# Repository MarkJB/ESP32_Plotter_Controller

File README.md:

# ESP32 Plotter Controller PCB
 
Released under an MIT licence, no warranty implied or given, use at own risk etc etc.

This is a two axis stepper controller based on the ESP32 and TMC2130 stepper drivers. It is intended to be used with drawing machines and plotters.

See https://github.com/MarkJB/TMC429_Daughterboard_for_ESP32_Plotter_Controller for the TMC429 (Hardware stepper driver contoller) daughter board for this board (plugs into the two stepper motor driver sockets and provides an extra axis and hardware acceleration control.

Firmware https://github.com/MarkJB/Grbl_Esp32 (This is a Fork of Grbl_Esp32, if its out of date, you probably only need the config file from this fork). Tested with standard and corexy kinematics and a solenoid/relay for the spindle.

First board revision A (aka 'Diamiond Chimp'), this board revision B (aka Emerald Dingo)

[Schematic]( https://github.com/MarkJB/ESP32_Plotter_Controller/blob/main/ESP32_Plotter_Controller_Schematic_RevA.pdf )

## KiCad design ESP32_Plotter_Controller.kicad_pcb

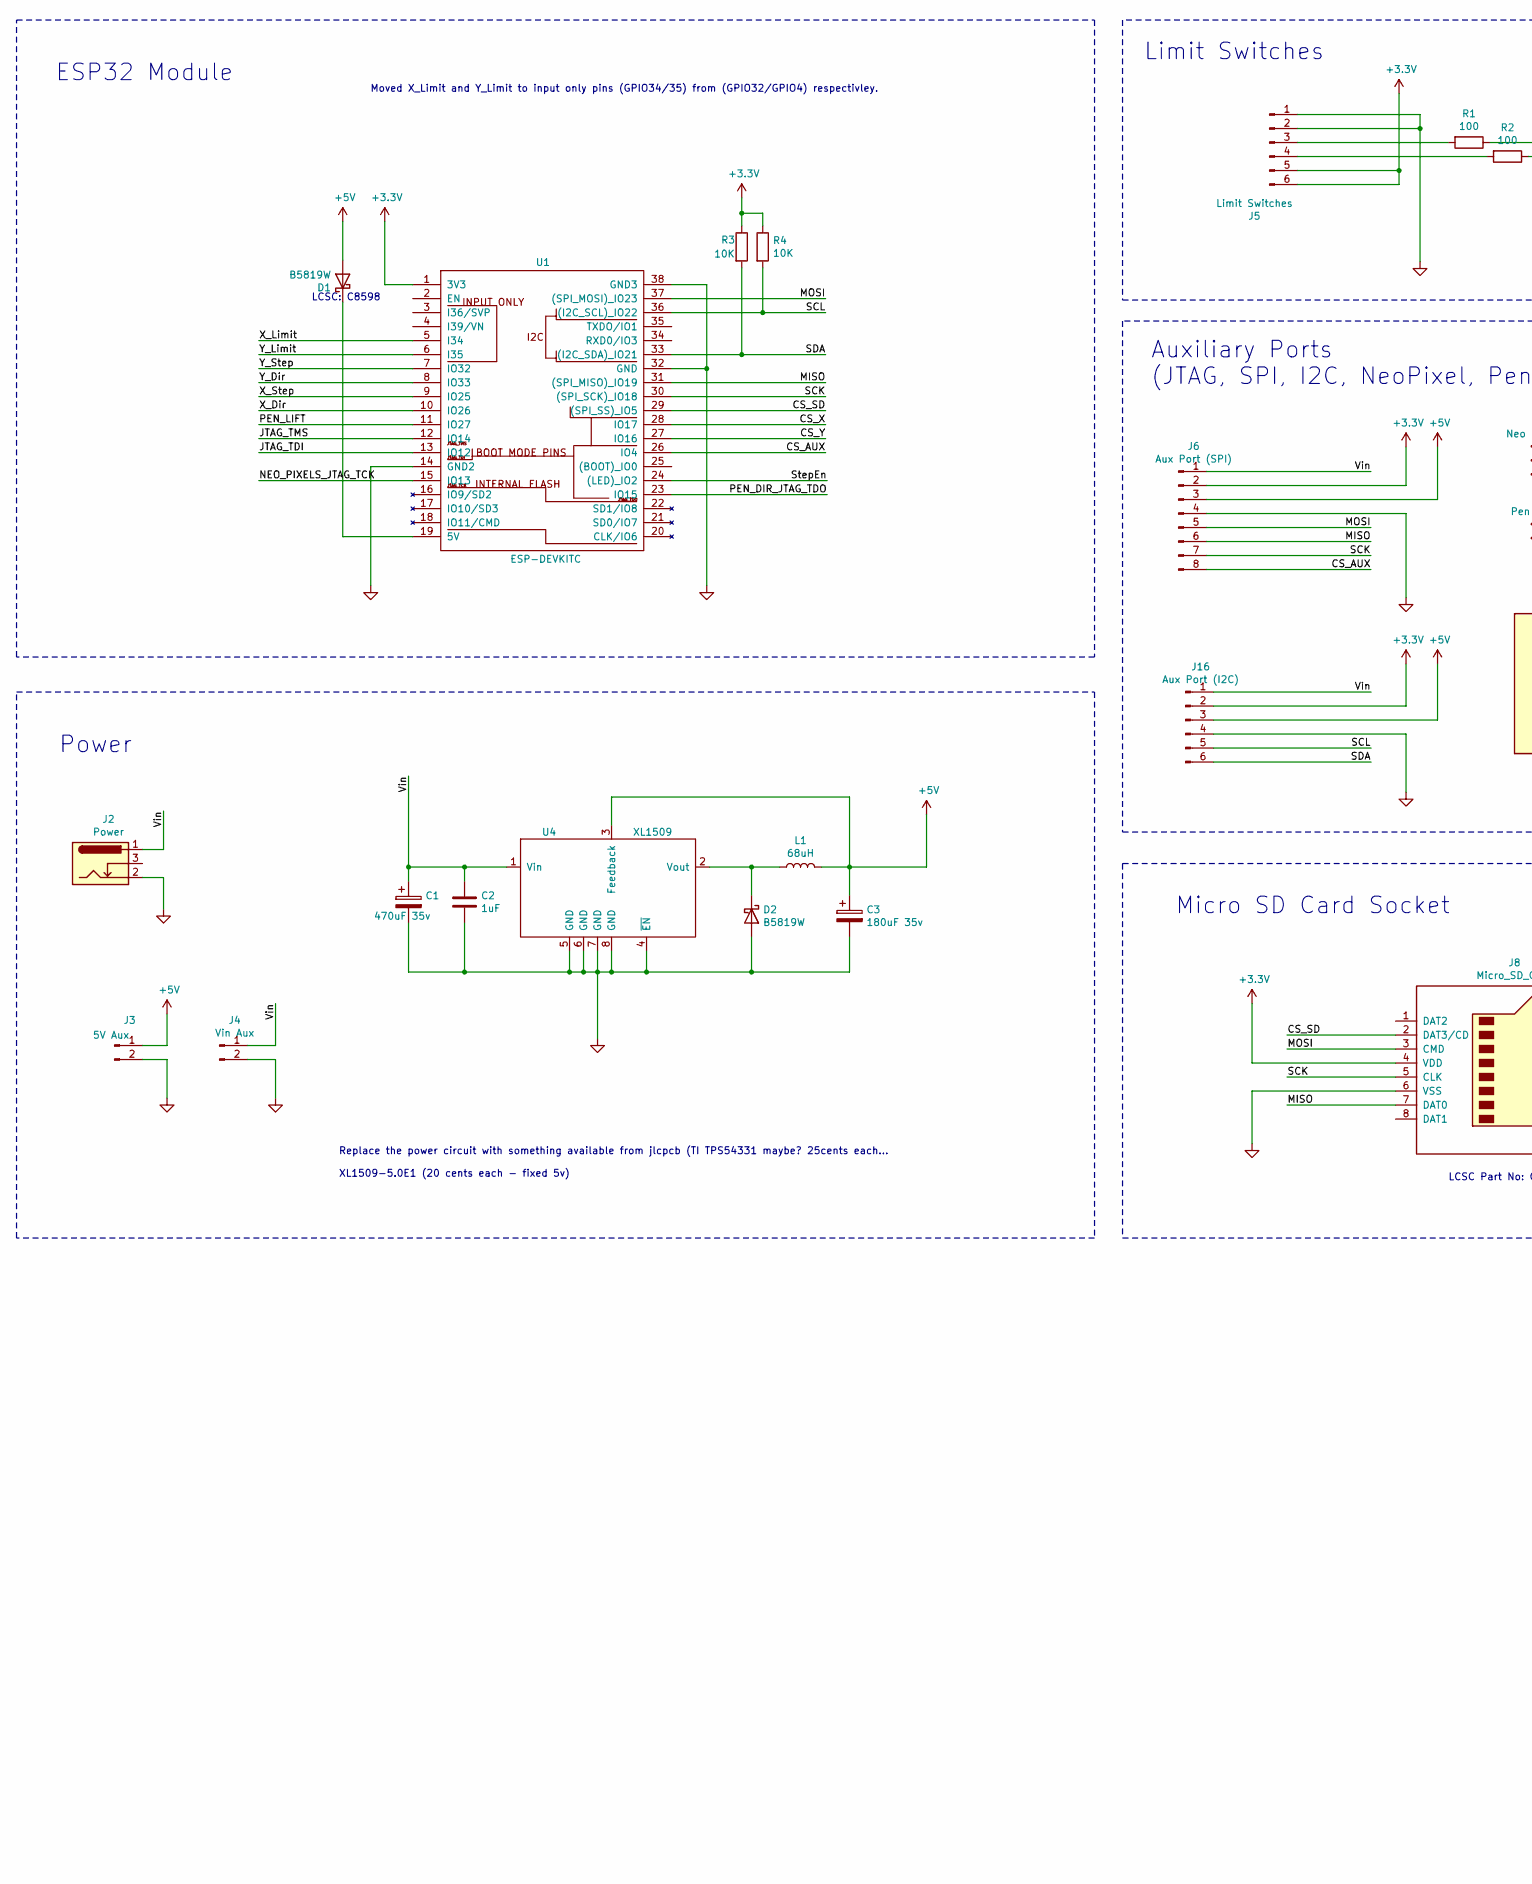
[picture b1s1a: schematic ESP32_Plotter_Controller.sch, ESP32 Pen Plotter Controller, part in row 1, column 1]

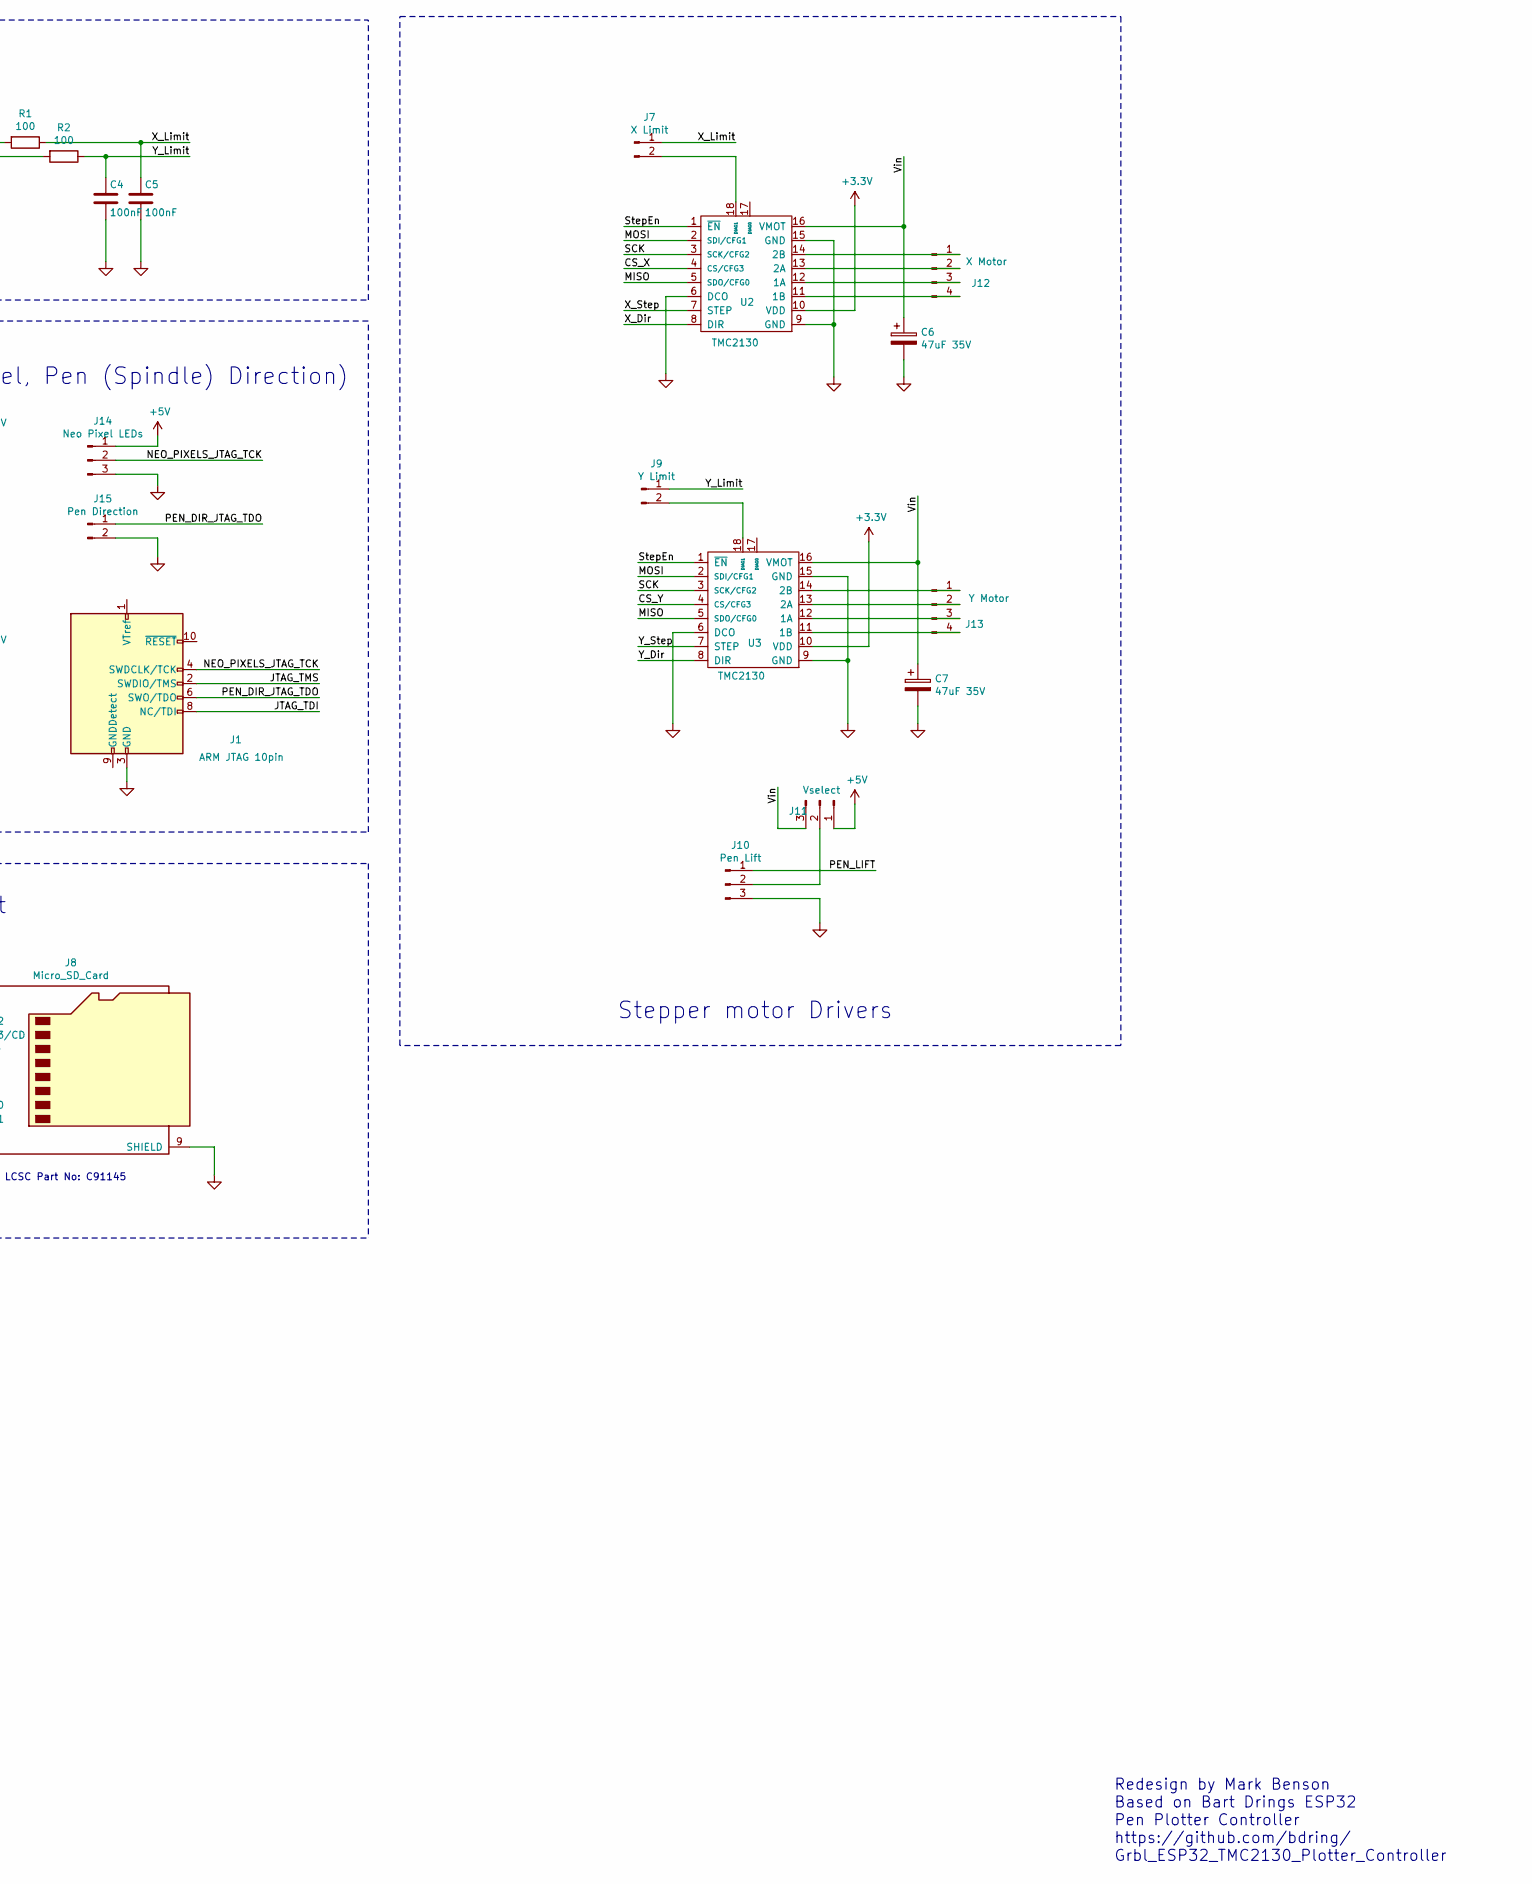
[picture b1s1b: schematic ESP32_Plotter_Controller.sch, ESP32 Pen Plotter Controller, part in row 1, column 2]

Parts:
C1: 470uF 35v; CP_Elec_10x10
C2: 1uF; C_0805_2012Metric
C3: 180uF 35v; CP_Elec_6.3x7.7
C4, C5: 100nF; C_0603_1608Metric
C6, C7: 47uF 35V; CP_Elec_6.3x5.7
D1, D2: B5819W; D_SOD-123
J1: ARM JTAG 10pin; PinSocket_2x05_P2.54mm_Vertical
J2: Power; BarrelJack_Horizontal
J3: 5V Aux; PinHeader_1x02_P2.54mm_Horizontal
J4: Vin Aux; PinHeader_1x02_P2.54mm_Horizontal
J5: Limit Switches; PinHeader_2x03_P2.54mm_Horizontal
J6: Aux Port (SPI); PinHeader_1x08_P2.54mm_Horizontal
J7: X Limit; PinHeader_1x02_P2.54mm_Vertical
J8: Micro_SD_Card; HK-TF01A
J9: Y Limit; PinHeader_1x02_P2.54mm_Vertical
J10: Pen Lift; PinHeader_1x03_P2.54mm_Horizontal
J11: Vselect; PinHeader_1x03_P2.54mm_Vertical
J12: X Motor; PinHeader_1x04_P2.54mm_Horizontal
J13: Y Motor; PinHeader_1x04_P2.54mm_Horizontal
J14: Neo Pixel LEDs; PinHeader_1x03_P2.54mm_Horizontal
J15: Pen Direction; PinHeader_1x02_P2.54mm_Horizontal
J16: Aux Port (I2C); PinHeader_1x06_P2.54mm_Horizontal
L1: 68uH; L_12x12mm_H6mm
R1, R2: 100; R_0603_1608Metric
R3, R4: 10K; R_0603_1608Metric
U1: ESP-DEVKITC; DEVKITC
U2, U3: TMC2130; StepstickTMCv2
U4: XL1509; SO-8_3.9x4.9mm_P1.27mm

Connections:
+3V3: J5.5, J5.6, J6.2, J8.4 (VDD), J16.2, R3.1, R4.1, U1.1 (3V3), U2.10 (VDD), U3.10 (VDD)
+5V: C3.1, D1.2 (A), J3.1, J6.3, J11.1, J14.1, J16.3, L1.2, U4.3 (Feedback)
/CS_AUX: J6.8, U1.26 (IO4)
/CS_SD: J8.2 (DAT3/CD), U1.29 ((SPI_SS)_IO5)
/CS_X: U1.28 (IO17), U2.4 (CS/CFG3)
/CS_Y: U1.27 (IO16), U3.4 (CS/CFG3)
/JTAG_TDI: J1.8 (NC/TDI), U1.13 (IO12)
/JTAG_TMS: J1.2 (SWDIO/TMS), U1.12 (IO14)
/MISO: J6.6, J8.7 (DAT0), U1.31 ((SPI_MISO)_IO19), U2.5 (SDO/CFG0), U3.5 (SDO/CFG0)
/MOSI: J6.5, J8.3 (CMD), U1.37 ((SPI_MOSI)_IO23), U2.2 (SDI/CFG1), U3.2 (SDI/CFG1)
/NEO_PIXELS_JTAG_TCK: J1.4 (SWDCLK/TCK), J14.2, U1.15 (IO13)
/PEN_DIR_JTAG_TDO: J1.6 (SWO/TDO), J15.1, U1.23 (IO15)
/PEN_LIFT: J10.1, U1.11 (IO27)
/SCK: J6.7, J8.5 (CLK), U1.30 ((SPI_SCK)_IO18), U2.3 (SCK/CFG2), U3.3 (SCK/CFG2)
/SCL: J16.5, R4.2, U1.36 ((I2C_SCL)_IO22)
/SDA: J16.6, R3.2, U1.33 ((I2C_SDA)_IO21)
/StepEn: U1.24 ((LED)_IO2), U2.1 (~EN), U3.1 (~EN)
/Vin: C1.1, C2.1, C6.1, C7.1, J2.1, J4.1, J6.1, J11.3, J16.1, U2.16 (VMOT), U3.16 (VMOT), U4.1 (Vin)
/X_Dir: U1.10 (IO26), U2.8 (DIR)
/X_Limit: C5.1, J7.1, R1.1, U1.5 (I34)
/X_Step: U1.9 (IO25), U2.7 (STEP)
/Y_Dir: U1.8 (IO33), U3.8 (DIR)
/Y_Limit: C4.1, J9.1, R2.1, U1.6 (I35)
/Y_Step: U1.7 (IO32), U3.7 (STEP)
GND: C1.2, C2.2, C3.2, C4.2, C5.2, C6.2, C7.2, D2.2 (A), J1.3 (GND), J1.5 (GND), J2.2, J3.2, J4.2, J5.1, J5.2, J6.4, J8.6 (VSS), J8.9 (SHIELD), J10.3, J14.3, J15.2, J16.4, U1.14 (GND2), U1.32 (GND), U1.38 (GND3), U2.6 (DCO), U2.9 (GND), U2.15 (GND), U3.6 (DCO), U3.9 (GND), U3.15 (GND), U4.4 (~EN), U4.5 (GND), U4.6 (GND), U4.7 (GND), U4.8 (GND)
unnamed: D1.1 (K), U1.19 (5V)
unnamed: D2.1 (K), L1.1, U4.2 (Vout)
unnamed: J5.3, R1.2
unnamed: J5.4, R2.2
unnamed: J7.2, U2.18 (DIAG1)
unnamed: J9.2, U3.18 (DIAG1)
unnamed: J10.2, J11.2
unnamed: J12.1, U2.14 (2B)
unnamed: J12.2, U2.13 (2A)
unnamed: J12.3, U2.12 (1A)
unnamed: J12.4, U2.11 (1B)
unnamed: J13.1, U3.14 (2B)
unnamed: J13.2, U3.13 (2A)
unnamed: J13.3, U3.12 (1A)
unnamed: J13.4, U3.11 (1B)

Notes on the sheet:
Micro SD Card Socket
Limit Switches
Stepper motor Drivers
ESP32 Module
Power
Replace the power circuit with something available from jlcpcb (TI TPS54331 maybe? 25cents each... XL1509-5.0E1 (20 cents each - fixed 5v)
LCSC: C8598
Redesign by Mark Benson Based on Bart Drings ESP32 Pen Plotter Controller https://github.com/bdring/ Grbl_ESP32_TMC2130_Plotter_Controller
Auxiliary Ports (JTAG, SPI, I2C, NeoPixel, Pen (Spindle) Direction)
Moved X_Limit and Y_Limit to input only pins (GPIO34/35) from (GPIO32/GPIO4) respectivley.
LCSC Part No: C91145

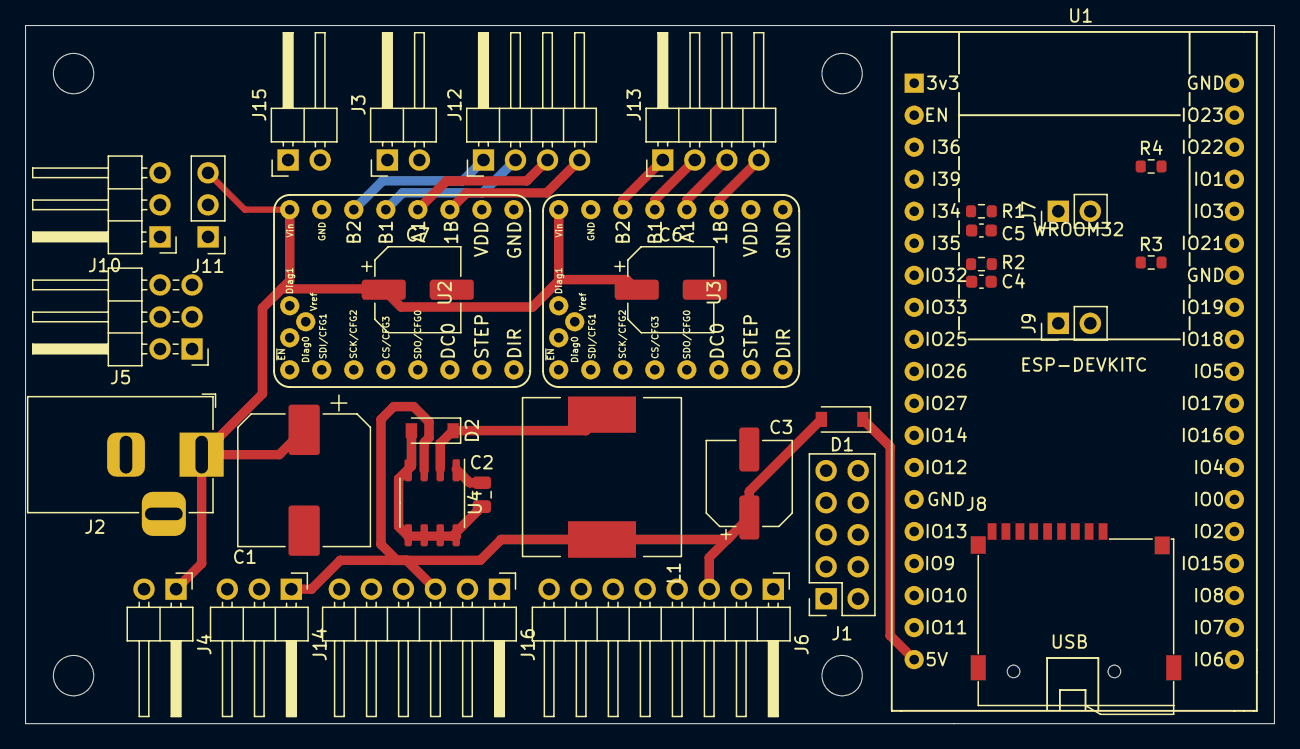
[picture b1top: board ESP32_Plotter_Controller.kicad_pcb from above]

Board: 2 copper layers, 99.1 x 55.4 mm, 38 parts (0 on the bottom side), 40 nets.

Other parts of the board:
H1, H2, H3, H4: MountingHole_3.2mm_M3

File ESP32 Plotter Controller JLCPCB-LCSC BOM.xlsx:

| ESP32 Plotter Controller parts cross check
 | PCB Part # | Value | Package | Board Note | Check Footprint | JLC part | JLC price | Package | LCSC part | LCSC price | Package | Qty (per board)
 | J1 | n/a | 5x2 vertical female 2.54mm | JTAG | TBD | No |  |  | C492399 | 0.14879999999999999 |  | 1
 | J2 | DC-005-20A | DC Barel jack | Power in | TBD | Yes | 0.17899999999999999 | 14.2*9.0mm | C130239 | 0.1023 |  | 1
 | J3 | n/a | 2x1 right angle male 2.54mm | 5v aux | n/a | Yes | 4.8999999999999998E-3 |  | C492410 | 1.2E-2 |  | 1
 | J4 | n/a | 2x1 right angle male 2.54mm | 12v aux | n/a | Yes | 4.8999999999999998E-3 |  | C492410 | 1.2E-2 |  | 1
 | J5 | n/a | 3x2 right angle male 2.54mm | Limit Switches | n/a | No |  |  | C358705 | 3.4200000000000001E-2 |  | 1
 | J6 | n/a | 8x1 right angle male 2.54mm | SPI port | n/a | No |  |  | C376126 | 4.8099999999999997E-2 |  | 1
 | J7 | n/a | 2x1 vertical male 2.54mm | X Limit en | n/a | Yes | 4.8999999999999998E-3 |  | C492401 | 4.8999999999999998E-3 |  | 1
 | J8 | n/a | Micro SD card socket | SD card female | TBD | No |  |  | C91145 | 0.17799999999999999 |  | 1
 | J9 | n/a | 2x1 vertical male 2.54mm | Y Limit en | n/a | Yes | 4.8999999999999998E-3 |  | C492401 | 4.8999999999999998E-3 |  | 1
 | J10 | n/a | 3x1 right angle male 2.54mm | Pen Lift | n/a | No |  |  | C492411 | 1.9900000000000001E-2 |  | 1
 | J11 | n/a | 3x1 vertical male 2.54mm | Pen Lift voltage select | n/a | No |  |  | C306223 | 0.34499999999999997 |  | 1
 | J12 | n/a | 4x1 right angle male 2.54mm | X Motor | n/a | No |  |  | C91552 | 1.89E-2 |  | 1
 | J13 | n/a | 4x1 right angle male 2.54mm | Y Motor | n/a | No |  |  | C91552 | 1.89E-2 |  | 1
 | J14 | n/a | 3x1 right angle male 2.54mm | Neo Pixels | n/a | No |  |  | C492411 | 1.9900000000000001E-2 |  | 1
 | J15 | n/a | 2x1 right angle male 2.54mm | Pen Direction | n/a | Yes | 4.8999999999999998E-3 |  | C492410 | 1.2E-2 |  | 1
 | U1 | n/a | 19x1 vertical female 2.54mm | ESP32 DevkitC | TBD | No |  |  | C319202 | 0.1119 |  | 1
 | U1 | n/a | 19x1 vertical female 2.54mm | ESP32 DevkitC | TBD | No |  |  | C319202 | 0.1119 |  | 1
 | U2 | n/a | 8x1 vertical female 2.54mm | TMC2130 Stepper X | TBC | No |  |  | C429957 | 6.2199999999999998E-2 |  | 1
 | U2 | n/a | 8x1 vertical female 2.54mm | TMC2130 Stepper X | TBC | No |  |  | C429957 | 6.2199999999999998E-2 |  | 1
 | U2 | n/a | 2x1 vertical female 2.54mm | TMC2130 Stepper X | TBC | No |  |  | C541849 | 7.2300000000000003E-2 |  | 1
 | U3 | n/a | 8x1 vertical female 2.54mm | TMC2130 Stepper Y | TBC | No |  |  | C429957 | 6.2199999999999998E-2 |  | 1
 | U3 | n/a | 8x1 vertical female 2.54mm | TMC2130 Stepper Y | TBC | No |  |  | C429957 | 6.2199999999999998E-2 |  | 1
 | U3 | n/a | 2x1 vertical female 2.54mm | TMC2130 Stepper Y | TBC | No |  |  | C541849 | 7.2300000000000003E-2 |  | 1
 | U4 | XL1509 | SO-8_3.9x4.9mm_P1.27mm | DCDC converter | TBC |  |  |  | C61063 | 0.2268 |  | 1
 | D1 | B5819W | SOD-123 | Reverse current protection | TBC | Yes | 3.44E-2 | SOD-123 | C8598 | 4.0399999999999998E-2 |  | 1
 | D2 | B5819W | SOD-123 | DCDC converter | TBC | Yes | 3.44E-2 | SOD-123 | C8598 | 4.0399999999999998E-2 |  | 1
 | C1 | 470uF 25v SMT Elec | CP_ELEC_10x10 | DCDC converter | TBC | No |  |  | C280412 | 0.1255 |  | 1
 | C2 | 1uF 25v | 0805 | DCDC converter | TBC | Yes | 5.2600000000000001E-2 |  | C28323 | 1.6299999999999999E-2 |  | 1
 | C3 | 180uF 25v SMT Elec | CP_ELEC_6.3x7.7 | DCDC converter | TBC | Yes | 0.16600000000000001 |  | C413657 | 0.30330000000000001 |  | 1
 | C4 | 100nF | 0603 | Y Limit debounce | TBC | No |  |  | C42998 | 3.2000000000000002E-3 |  | 1
 | C5 | 100nF | 0603 | X Limit debounce | TBC | No |  |  | C42998 | 3.2000000000000002E-3 |  | 1
 | R1 | 100R | 0603 | X Limit debounce | TBC | Yes | 1.2999999999999999E-3 |  | C25201 | 1.2999999999999999E-3 |  | 1
 | R2 | 100R | 0603 | Y Limit debounce | TBC | Yes | 1.2999999999999999E-3 |  | C25201 | 1.2999999999999999E-3 |  | 1
 | R3 | 10K | 0603 | I2C Pull up (SDA) | TBC | No |  |  | C98220 | 1.5E-3 |  | 1
 | R4 | 10K | 0603 | I2C Pull up (SCL) | TBC | No |  |  | C98220 | 1.5E-3 |  | 1
 | L1 | 68uH 1.5A | SMD, 12.3x12.3x6mm | DCDC converter | TBC |  |  |  | C439406 | 0.23200000000000001 |  | 1
 | PCB | Guestimate |  |  |  |  |  |  |  | 5
 | Assembly | Guestimate |  |  |  |  |  |  |  | 5
 |  |  |  |  |  |  |  |  |  | 12.593700000000002
 | Order BOM
 | LCSC Part No: | Qty | PCB Part No: | Package | Value | Cost
 | C492399 | 1 | J1 | 5x2 vertical female 2.54mm
 | C130239 | 1 | J2 | DC Barrel jack
 | C492410 | 2 | J3, J4, J15 | 2x1 right angle male 2.54mm
 | C358705 | 1 | J5 | 3x2 right angle male 2.54mm
 | C376126 | 1 | J6 | 8x1 right angle male 2.54mm
 | C492401 | 2 | J7, J9 | 2x1 vertical male 2.54mm
 | C492411 | 2 | J10, J14 | 3x1 right angle male 2.54mm
 | C306223 | 1 | J11 | 3x1 vertical male 2.54mm
 | C91552 | 2 | J12, J13 | 4x1 right angle male 2.54mm
 | C91145 | 1 | J8 | Micro SD card socket
 | C319202 | 2 | U1 | 19x1 vertical female 2.54mm
 | C429957 | 4 | U2, U3 A | 8x1 vertical female 2.54mm
 | C541849 | 2 | U2, U3 B | 2x1 vertical female 2.54mm
 | C8598 | 2 | D1, D2 | SOD-123 | B5819W
 | C280412 | 1 | C1 | CP_ELEC_10x10 | 470uF 25v SMT Elec
 | C28323 | 1 | C2 | 805 | 1uF 25v ceramic
 | C413657 | 1 | C3 | CP_ELEC_6.3x7.7 | 180uF 25v SMT Elec
 | C42998 | 2 | C4, C5 | 603 | 100nF ceramic
 |  | 2 | C6, C7 |  | 47uF 25v SMT Elec
 | C25201 | 2 | R1, R2 | 603 | 100R
 | C98220 | 2 | R3, R4 | 603 | 10k
 | C439406 | 1 | L1 | L_12.3x12.3x6 SMT | 68uH 1.5A

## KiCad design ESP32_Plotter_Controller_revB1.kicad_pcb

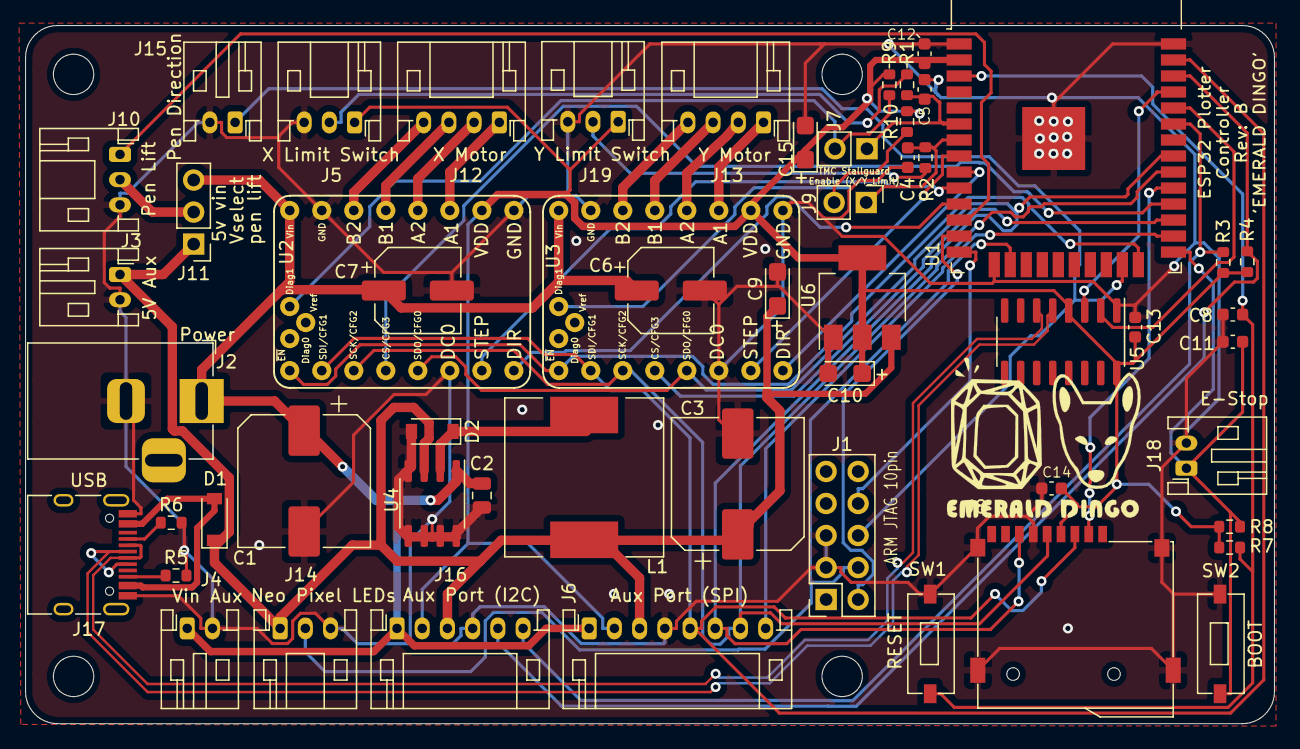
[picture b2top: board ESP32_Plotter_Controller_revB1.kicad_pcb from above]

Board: 2 copper layers, 99.1 x 55.4 mm, 61 parts (1 on the bottom side), 48 nets.

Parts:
C1: 470uF 35v; CP_Elec_10x10
C2: 1uF; C_0805_2012Metric
C3: 220uF 50v; CP_Elec_10x10
C4, C5, C8, C11, C12, C13, C14: 100nF; C_0603_1608Metric
C6, C7: 47uF 35V; CP_Elec_6.3x5.7
C9, C10, C15: 22uF 10v; CP_EIA-3216-18_Kemet-A
D1, D2: B5819W; D_SOD-123
G1: LOGO; emerald_dingo_400
G2: LOGO; emerald_dingo_150
H1, H2, H3, H4: MountingHole_3.2mm_M3
J1: ARM JTAG 10pin; PinSocket_2x05_P2.54mm_Vertical
J2: Power; BarrelJack_Horizontal
J3: 5V Aux; JST_PH_S2B-PH-K_1x02_P2.00mm_Horizontal
J4: Vin Aux; JST_PH_S2B-PH-K_1x02_P2.00mm_Horizontal
J5: X Limit Switch; JST_PH_S3B-PH-K_1x03_P2.00mm_Horizontal
J6: Aux Port (SPI); JST_PH_S8B-PH-K_1x08_P2.00mm_Horizontal
J7: X Limit; PinHeader_1x02_P2.54mm_Vertical
J8: Micro_SD_Card_TF-01A; HK-TF01A
J9: Y Limit; PinHeader_1x02_P2.54mm_Vertical
J10: Pen Lift; JST_PH_S3B-PH-K_1x03_P2.00mm_Horizontal
J11: Vselect; PinHeader_1x03_P2.54mm_Vertical
J12: X Motor; JST_PH_S4B-PH-K_1x04_P2.00mm_Horizontal
J13: Y Motor; JST_PH_S4B-PH-K_1x04_P2.00mm_Horizontal
J14: Neo Pixel LEDs; JST_PH_S3B-PH-K_1x03_P2.00mm_Horizontal
J15: Pen Direction; JST_PH_S2B-PH-K_1x02_P2.00mm_Horizontal
J16: Aux Port (I2C); JST_PH_S6B-PH-K_1x06_P2.00mm_Horizontal
J17: USB_C_Receptacle_USB2.0; USB_C_Receptacle_HRO_TYPE-C-31-M-12
J18: E-Stop; JST_PH_S2B-PH-K_1x02_P2.00mm_Horizontal
J19: Y Limit Switch; JST_PH_S3B-PH-K_1x03_P2.00mm_Horizontal
L1: 68uH; L_12x12mm_H6mm
R1, R2: 100; R_0603_1608Metric
R3, R4, R7, R8, R9, R10: 10k; R_0603_1608Metric
R5, R6: 5.1k; R_0603_1608Metric
SW1: RESET; K2-1107ST
SW2: BOOT; K2-1107ST
U1: ESP32-WROOM-32D; ESP32-WROOM-32
U2, U3: TMC2130; StepstickTMCv2
U4: XL1509; SO-8_3.9x4.9mm_P1.27mm
U5: CH340C; SOIC-16_3.9x9.9mm_P1.27mm
U6: AMS1117-3.3; SOT-223-3_TabPin2

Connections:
+3V3: C10.1, C12.1, C13.1, C14.1, C15.1, J5.1, J6.2, J8.4, J16.2, J19.1, R3.1, R4.1, R7.2, R8.1, R9.1, R10.1, U1.2, U2.10, U3.10, U5.4, U5.16, U6.2
+5V: C3.1, C9.1, D1.1, J3.1, J6.3, J11.1, J14.1, J16.3, L1.2, U4.3, U6.3
/CS_AUX: J6.8, U1.26
/CS_SD: J8.2, U1.29
/CS_X: U1.28, U2.4
/CS_Y: U1.27, U3.4
/D+: J17.A6, J17.B6, U5.5
/D-: J17.A7, J17.B7, U5.6
/EN: C8.2, R7.1, SW1.2, U1.3
/ESP32_RX: U1.34, U5.2
/ESP32_TX: U1.35, U5.3
/IO0: C11.1, J18.1, R8.2, SW2.2, U1.25
/JTAG_TDI: J1.8, U1.14
/JTAG_TMS: J1.2, U1.13
/MISO: J6.6, J8.7, U1.31, U2.5, U3.5
/MOSI: J6.5, J8.3, U1.37, U2.2, U3.2
/NEO_PIXELS_JTAG_TCK: J1.4, J14.2, U1.16
/PEN_DIR_JTAG_TDO: J1.6, J15.1, U1.23
/PEN_LIFT: J10.1, U1.12
/SCK: J6.7, J8.5, U1.30, U2.3, U3.3
/SCL: J16.5, R4.2, U1.36
/SDA: J16.6, R3.2, U1.33
/StepEn: U1.24, U2.1, U3.1
/Vin: C1.1, C2.1, C6.1, C7.1, J2.1, J4.1, J6.1, J11.3, J16.1, U2.16, U3.16, U4.1
/X_Dir: U1.11, U2.8
/X_Limit: C5.1, J7.1, R1.1, U1.6
/X_Step: U1.10, U2.7
/Y_Dir: U1.9, U3.8
/Y_Limit: C4.1, J9.1, R2.1, U1.7
/Y_Step: U1.8, U3.7
GND: C1.2, C2.2, C3.2, C4.2, C5.2, C6.2, C7.2, C8.1, C9.2, C10.2, C11.2, C12.2, C13.2, C14.2, C15.2, D2.2, J1.3, J1.5, J2.2, J3.2, J4.2, J5.3, J6.4, J8.6, J8.10, J8.11, J8.12, J8.13, J10.3, J14.3, J15.2, J16.4, J17.A1, J17.A12, J17.B1, J17.B12, J18.2, J19.3, R5.2, R6.2, SW1.1, SW2.1, U1.1, U1.15, U1.38, U1.39, U2.6, U2.9, U2.15, U3.6, U3.9, U3.15, U4.4, U4.5, U4.6, U4.7, U4.8, U5.1, U6.1
unnamed: D1.2, J17.A4, J17.A9, J17.B4, J17.B9
unnamed: D2.1, L1.1, U4.2
unnamed: J5.2, R1.2
unnamed: J7.2, R9.2, U2.18
unnamed: J9.2, R10.2, U3.18
unnamed: J10.2, J11.2
unnamed: J12.1, U2.11
unnamed: J12.2, U2.12
unnamed: J12.3, U2.13
unnamed: J12.4, U2.14
unnamed: J13.1, U3.11
unnamed: J13.2, U3.12
unnamed: J13.3, U3.13
unnamed: J13.4, U3.14
unnamed: J17.A5, R6.1
unnamed: J17.B5, R5.1
unnamed: J19.2, R2.2

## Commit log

2021-02-18 Clean up
2021-02-20 Clean up folder
2021-02-20 Clean up, add repo name
2021-02-20 Removed unused models and foot prints
2021-02-20 Remove venv
2021-02-20 Update images and 3d model
2021-03-04 Fix DCDC track layout
2021-03-08 Increased thickness of 5v track to J3
    J3 (5v Aux) was a 0.25mm track. Increased to 0.4mm.
2021-04-05 Fix sdcard footprint
    Fix mirrored pinout on SD Card footprint.
    Also grounded shield in schematic and disconnected the sd insert sense pin from gnd.
2021-04-15 Pinmap & new grber files for sd card fix
2021-09-21 Misc changes
    Not sure what I changed here, but the current production boards were made from this set of files.
2021-09-27 Use ESP32 module and CH340C for comms
2021-09-28 Associate footprints
2021-09-28 First pass at placing components
2021-10-02 Updated component association
    Lost some footprint associations, but also changed some footprints to use alternative components from LCSC
2021-10-02 Replace connectors with JST PH
    Replace footprint associations with JST PH through hole right angle connectors and add associated LCSC part no (optimized for price and availability).
2021-10-02 First pass at placing components with JST connectors
2021-10-07 Updated components etc
    Used smaller buttons. Added custom footprint.
    JST PH 2.0 thru-hole right angle connectors.
    Connected USB 5v via diode to 3v3 regulator.
    Silkscreen updated.
2021-10-26 Tweaked component layout again
    Moved buttons, sdcard and usb chip around
2021-10-28 Change to USB C connector
    Had to move connectors around to make room.
2021-12-04 RevB1 commit before cleanup
    I wanted to be sure I didn't delete something I needed later, so this commit is all files in whatever state. In the next commit I will remove everything I think I no longer need so the repo is a bit 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
2021-12-04 RevB1 'Emerald Dingo'
    Version B1 with embedded ESP32
    USB C with CH340C chip
    Reset and boot buttons
    E-Stop and JST PH 2.00mm connectors
2022-01-08 Add pull-up resistors to EN and IO0
2022-01-08 Add LCSC part no for SD socket
2022-01-09 Fix SD card footprint and add pull-up resistors
    Rev B was using an old and incorrect footprint causing a 3.3v short to ground when an SD card was inserted. Update to use the fixed footprint.
    Added pull-up resistors for EN and IO0 (Boot mode). On test board, IO0 appeared to be pulled permanently low. It could be programmed but would not boot. It may only be necessary for EN to be pulled h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
2022-01-10 Add pull-ups and manually tweak some routes
    Added pull-ups for EN, Bpot, X_Limit & Y_Limit.
    Re-routed some tracks to improve thermal ground on ESP32 module and to allow for better Gnd fills.
    Regenerated Gerber files to include footprint values on front silkscreen.
2022-01-11 Silkscreen tweaks and remove unnecessary tracks from USB-C connector shield
2022-01-11 Update footprint 3d models
    Fixed broken paths.
2022-01-11 Update pinmap
2022-01-11 Show graphics from this branch
2022-01-23 Update component values
    Some 10k resistors were using the value 10k vs 10K so weren't grouped correctly.
    Some 100nF capacitors were shown as 0.1uF so weren't grouped correctly.
2022-01-23 Add decoupling capacitors
2022-01-23 Fix USB differential pair routing
2022-01-24 Tweaked some ground planes and silkscreen
2022-02-13 Fix screw head clearance problem with C15
    Decoupling cap for ESP32 would be in the way of an M3 screw head. Moved down to nearer J17. Clearance checked in CAD.
2022-02-15 Update LCSC part numbers and production files
2022-02-17 Change C3 COUT to 220uF
    220uF is more readily available from LCSC and can use a better quality capacitor
2022-02-19 Updated gerber files for RevB.04
2022-06-12 Fix typo on stepper driver footpint
2022-06-12 Update PCB with fixed stepper footprint
2022-06-12 Fix solenoid pinout on pinmap
    Had swapped GND and PEN_LIFT
